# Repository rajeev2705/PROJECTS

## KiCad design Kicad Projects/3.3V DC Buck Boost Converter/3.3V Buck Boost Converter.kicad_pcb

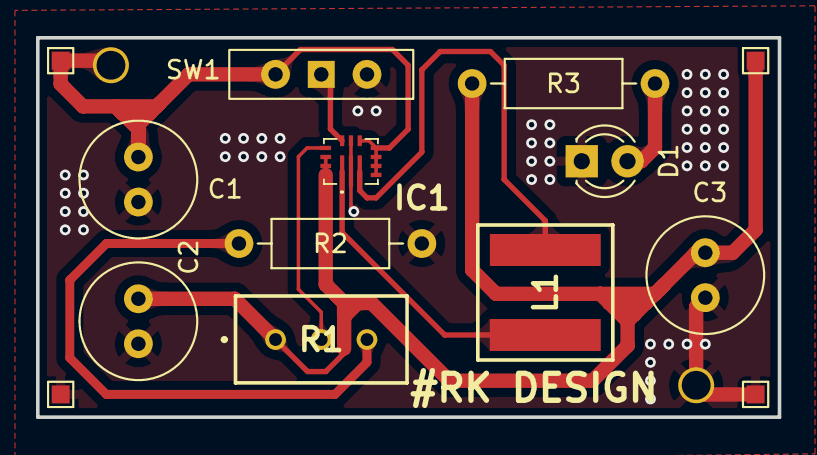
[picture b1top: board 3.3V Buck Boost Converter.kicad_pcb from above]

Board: 2 copper layers, 41.2 x 21.1 mm, 14 parts (0 on the bottom side), 9 nets.

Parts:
C1: 10uF/10V; C_Radial_D6.3mm_H11.0mm_P2.50mm
C2, C3: 22uf/6V3; C_Radial_D6.3mm_H11.0mm_P2.50mm
D1: LED; LED_D3.0mm
IC1: Buck_Boost_TPS63025_SMD; IC_BuckBoost_TPS630250RNCT_VQFN14_2x3mm
J1: VIN+; TestPoint_Pad_1.0x1.0mm
J2: VIN-; TestPoint_Pad_1.0x1.0mm
J3: VOUT+; TestPoint_Pad_1.0x1.0mm
J4: VOUT-; TestPoint_Pad_1.0x1.0mm
L1: L; XFL7015102MEB
R1: PT01-D120K1-B103; TrimPot_10k_SMD
R2: 180k; R_Axial_DIN0207_L6.3mm_D2.5mm_P10.16mm_Horizontal
R3: 1k; R_Axial_DIN0207_L6.3mm_D2.5mm_P10.16mm_Horizontal
SW1: SW_Wuerth_450301014042; SW_Slide-03_Wuerth-WS-SLTV_10x2.5x6.4_P2.54mm

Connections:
3V3: C2.1, C3.1, IC1.12 (VOUT_1), IC1.13 (VOUT_2), IC1.14 (VOUT_3), J3.1, R1.1, R3.1
FB: IC1.11 (FB), R1.2
GND: C1.2, C2.2, C3.2, D1.1 (K), IC1.2 (PGND), IC1.9 (GND), J2.1, J4.1, R2.1, SW1.2 (C)
unnamed: D1.2 (A), R3.2
unnamed: IC1.3 (L1), L1.1
unnamed: IC1.1 (L2), L1.2
unnamed: R1.3, R2.2
PFM/PWM: IC1.10 (PFM/PWM), SW1.1 (B)
VIN+: C1.1, IC1.4 (VIN_1), IC1.5 (VIN_2), IC1.6 (VIN_3), IC1.7 (VINA), IC1.8 (EN), J1.1, SW1.3 (A)

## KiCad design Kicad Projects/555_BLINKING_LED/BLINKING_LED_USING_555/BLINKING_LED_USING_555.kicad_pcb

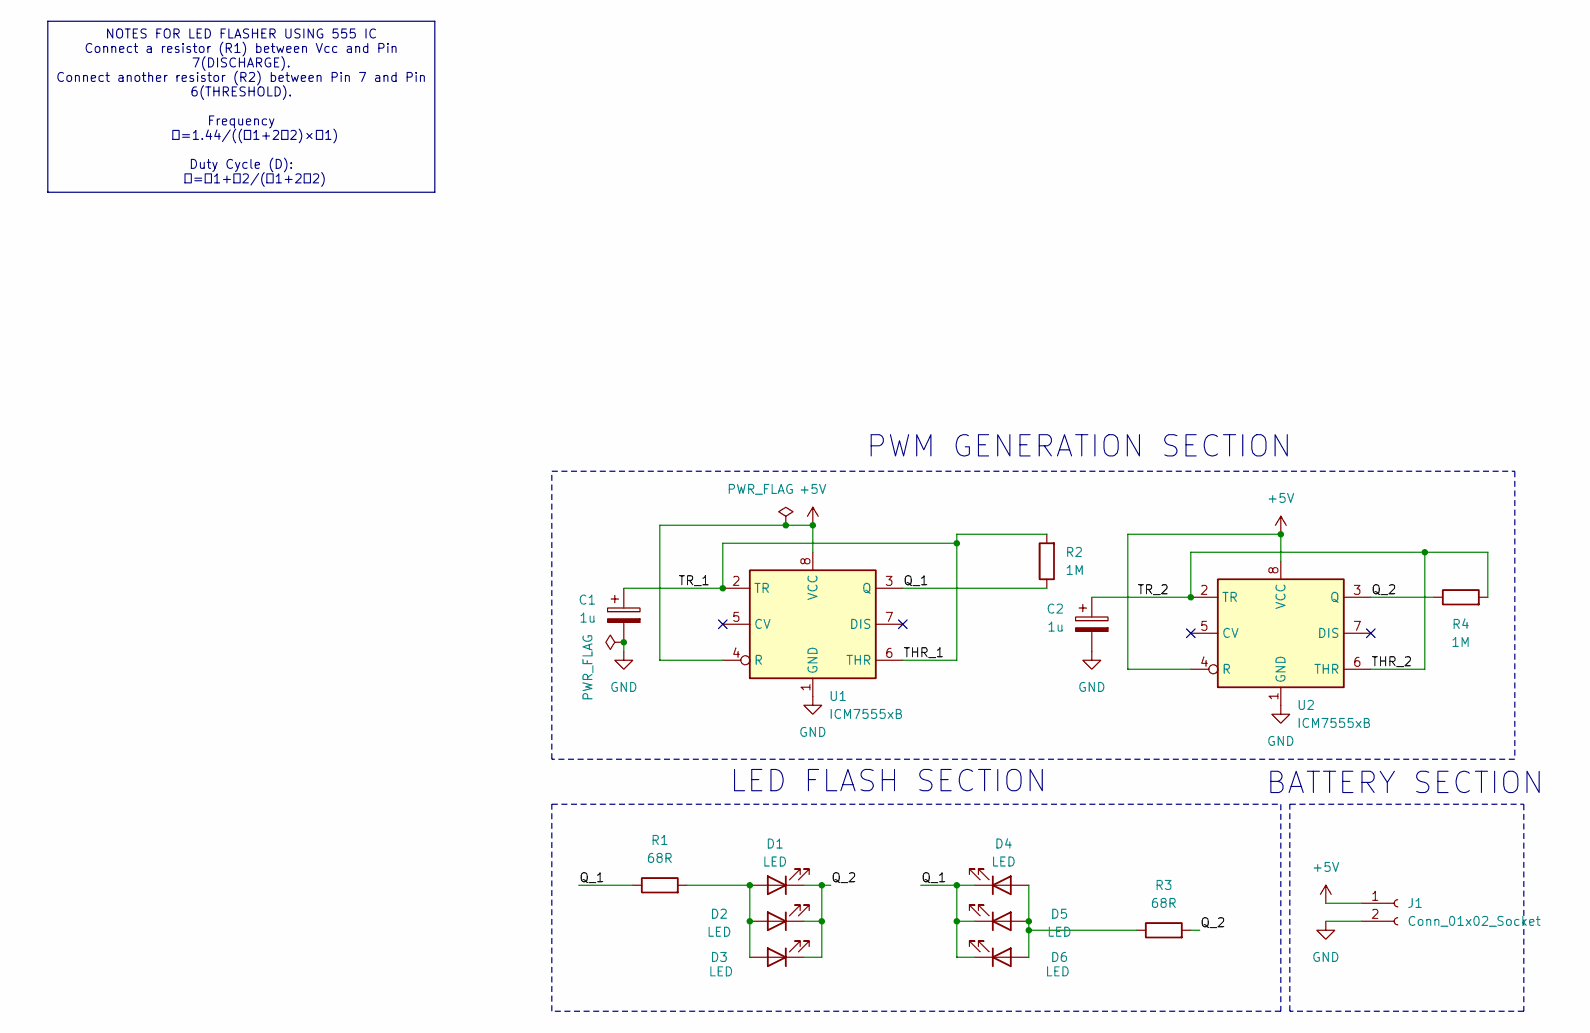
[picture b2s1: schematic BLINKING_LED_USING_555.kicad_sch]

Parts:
C1, C2: 1u; CP_Radial_D4.0mm_P1.50mm
D1, D2, D3, D4, D5, D6: LED; LED_D3.0mm
J1: Conn_01x02_Socket; PinHeader_1x02_P2.54mm_Vertical
R1: 68R; R_Axial_DIN0207_L6.3mm_D2.5mm_P7.62mm_Horizontal
R2, R4: 1M; R_Axial_DIN0207_L6.3mm_D2.5mm_P10.16mm_Horizontal
R3: 68R; R_Axial_DIN0207_L6.3mm_D2.5mm_P10.16mm_Horizontal
U1, U2: ICM7555xB; SOIC-8_3.9x4.9mm_P1.27mm

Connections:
+5V: J1.1, U1.4 (R), U1.8 (VCC), U2.4 (R), U2.8 (VCC)
/Q_1: D4.1 (K), D5.1 (K), D6.1 (K), R1.1, R2.1, U1.3 (Q)
/Q_2: D1.1 (K), D2.1 (K), D3.1 (K), R3.2, R4.1, U2.3 (Q)
/THR_1: C1.1, R2.2, U1.2 (TR), U1.6 (THR)
/THR_2: C2.1, R4.2, U2.2 (TR), U2.6 (THR)
GND: C1.2, C2.2, J1.2, U1.1 (GND), U2.1 (GND)
unnamed: D1.2 (A), D2.2 (A), D3.2 (A), R1.2
unnamed: D4.2 (A), D5.2 (A), D6.2 (A), R3.1

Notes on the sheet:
NOTES FOR LED FLASHER USING 555 IC Connect a resistor (R1) between Vcc and Pin 7(DISCHARGE). Connect another resistor (R2) between Pin 7 and Pin 6(THRESHOLD). Frequency 𝑓=1.44/((𝑅1+2𝑅2)×𝐶1) Duty Cycle (D): 𝐷=𝑅1+𝑅2/(𝑅1+2𝑅2)
LED FLASH SECTION
BATTERY SECTION
PWM GENERATION SECTION

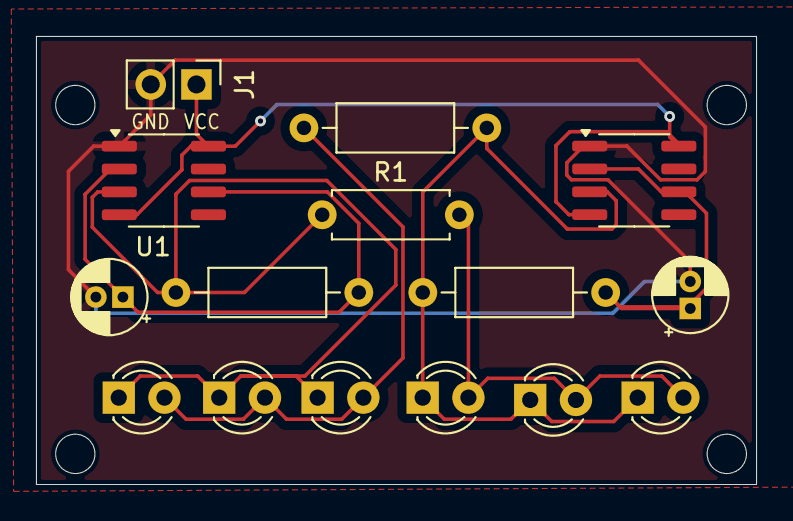
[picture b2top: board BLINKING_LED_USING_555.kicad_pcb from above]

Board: 2 copper layers, 40.0 x 24.9 mm, 15 parts (0 on the bottom side), 8 nets.

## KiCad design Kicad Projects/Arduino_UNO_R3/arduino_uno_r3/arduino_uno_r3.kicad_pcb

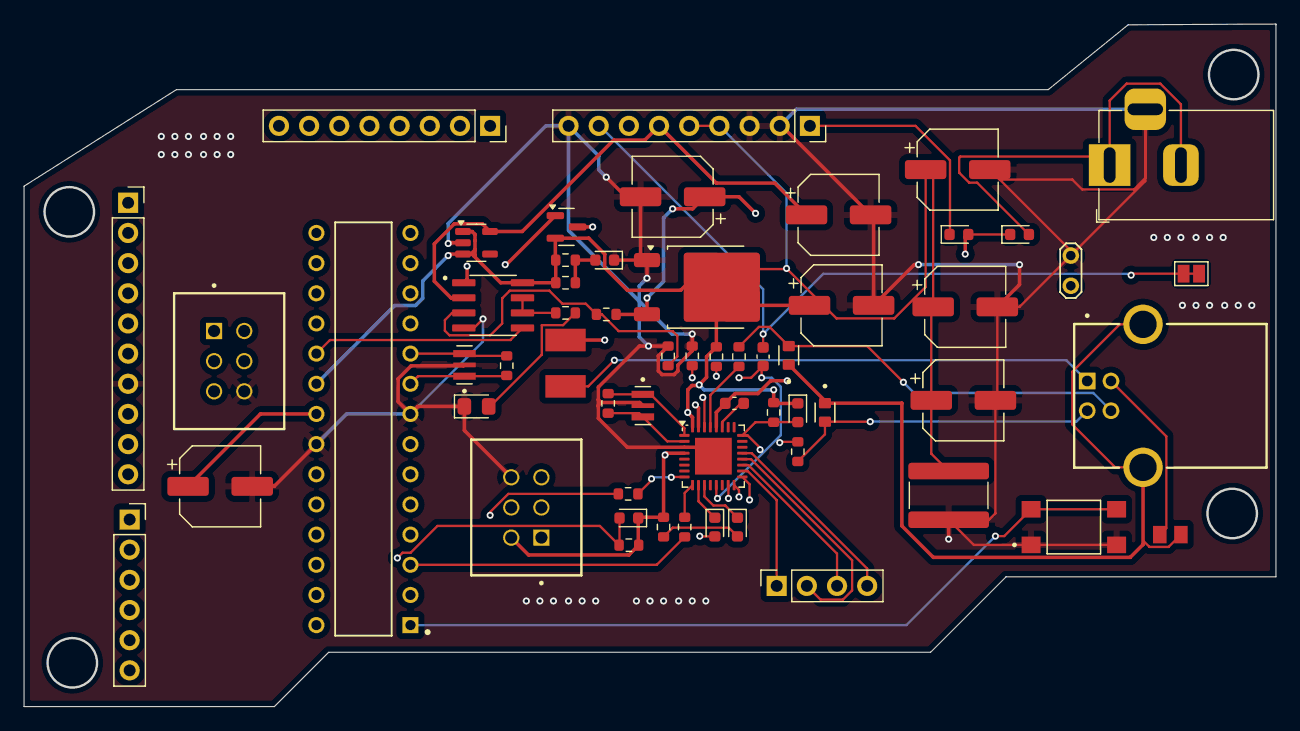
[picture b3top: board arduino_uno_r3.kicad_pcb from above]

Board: 4 copper layers, 105.4 x 57.5 mm, 58 parts (0 on the bottom side), 62 nets.

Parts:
C1, C2: 47u; CP_Elec_6.3x3
C3, C4, C9, C10: 100n; CP_Elec_6.3x3
C5: 1u; CP_Elec_6.3x3
C6: 1u; C_0603_1608Metric
C7: 100n; C_1825_4564Metric
C8: 100n; C_0603_1608Metric
D1, D3, D7, D8: D; D_0603_1608Metric
D2: GREEN ON; LED_0603_1608Metric
D4, D5: LED; LED_0603_1608Metric
D6: LED; LED_0805_2012Metric_Pad1.15x1.40mm_HandSolder
F1: MF-MSMF050-2; FUSM1812X02
FL1: BLM21SP111SH1D; BEADC2012X105N
J1: Barrel_Jack_Switch_Pin3Ring; BarrelJack_Horizontal
J2: Conn_01x09_Socket; PinSocket_1x09_P2.54mm_Vertical
J3: USB-B-S-X-X-TH-TR; SAMTEC_USB-B-S-X-X-TH-TR
J4, J6: ICSP HEADER; SAMTEC_TSS-103-03-L-D
J5: Conn_01x04_Socket; PinSocket_1x04_P2.54mm_Vertical
J7: Conn_01x08_Socket; PinSocket_1x08_P2.54mm_Vertical
J8: Conn_01x10_Socket; PinSocket_1x10_P2.54mm_Vertical
J9: Conn_01x06_Socket; PinSocket_1x06_P2.54mm_Vertical
JP1: SolderJumper_2_Open; SolderJumper-2_P1.3mm_Open_Pad1.0x1.5mm
JP2: SolderJumper_2_Open; TestPoint_2Pads_Pitch2.54mm_Drill0.8mm
Q1: FDN340P; SOT-23
R1A1, R1B1, R8, R9, R11, R12, R15, R16: 1k; R_0603_1608Metric
R3, R4, R5, R14: 10k; R_0603_1608Metric
R6, R7: 22R; R_0603_1608Metric
R10, R13: 1M; R_0603_1608Metric
RV1, RV2: CG0603MLC-05E; VARC1608X56N
S1: TL3305CF160QG; SW_TL3305CF160QG
U1: NCP1117-5.0_TO252; TO-252-2
U3: LP2985-3.3; SOT-23-5
U4: ATmega16U2-M; QFN-32-1EP_5x5mm_P0.5mm_EP3.1x3.1mm
U6: LMV358; SOIC127P599X175-8N
U7: ATMEGA328P-PU; DIP794W46P254L2967H457Q28B
Y1, Y2: CSTCE16M0V53-R0; OSC_CSTCE16M0V53-R0

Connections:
+5V: C2.1, C3.1, C4.1, C7.2, C10.1, D3.1 (K), D7.1 (K), J2.4, J2.5, J4.02, J6.02, Q1.2 (S), R1A1.2, R1B1.2, R5.2, R8.1, R9.1, R14.2, U1.2 (VO), U3.1 (VIN), U3.3 (ON/~OFF), U4.4 (VCC), U4.32 (AVCC), U6.8 (V+), U7.7 (VCC), U7.20 (AVCC)
/MCU/AREF: C9.1, J8.8, U7.21 (AREF)
/MCU/IO0/RXD: J7.1, R15.1, U7.2 (PD0)
/MCU/IO1/TXD: J7.2, R16.1, U7.3 (PD1)
/MCU/IO2: J7.3, U7.4 (PD2)
/MCU/IO3: J7.4, U7.5 (PD3)
/MCU/IO4: J7.5, U7.6 (PD4)
/MCU/IO5: J7.6, U7.11 (PD5)
/MCU/IO6: J7.7, U7.12 (PD6)
/MCU/IO7: J7.8, U7.13 (PD7)
/MCU/IO8: J8.1, U7.14 (PB0)
/MCU/IO9: J8.2, U7.15 (PB1)
/MCU/PB3/MOSI: J6.04, J8.4, U7.17 (PB3)
/MCU/PB4/MISO: J6.01, J8.5, U7.18 (PB4)
/MCU/PB5/SCK: J6.03, J8.6, U6.5 (+), U7.19 (PB5)
/MCU/PC0: J9.1, U7.23 (PC0)
/MCU/PC1: J9.2, U7.24 (PC1)
/MCU/PC2: J9.3, U7.25 (PC2)
/MCU/PC3: J9.4, U7.26 (PC3)
/MCU/PC4/SDA: J8.9, J9.5, U7.27 (PC4)
/MCU/PC5/SCL: J8.10, J9.6, U7.28 (PC5)
/MCU/RESET: D7.2 (A), J6.05, R14.1, S1.3, S1.4, U7.1 (PC6/~RESET)
/MCU/SS: J8.3, U7.16 (PB2)
/POWER SEC/+3.3V: C5.1, J2.6, U3.5 (VOUT), U6.2 (-)
/POWER SEC/GATE_CONTROL: Q1.1 (G), U6.1
/POWER SEC/PWRIN: D1.2 (A), J1.1, J1.2
/POWER SEC/VIN: C1.1, D1.1 (K), D8.2 (A), J2.7, R3.1, U1.3 (VI)
/USB SECTION/AT_TO_CAP: C6.1, U4.27 (UCAP)
/USB SECTION/MCUD+: R7.1, U4.29 (D+)
/USB SECTION/MCUD-: R6.1, U4.30 (D-)
/USB SECTION/MISO2: J4.01, U4.17 (PB3)
/USB SECTION/MOSI2: J4.04, U4.16 (PB2)
/USB SECTION/PB4: J5.1, U4.18 (PB4)
/USB SECTION/PB5: J5.3, U4.19 (PB5)
/USB SECTION/PB6: J5.2, U4.20 (PB6)
/USB SECTION/PB7: J5.4, U4.21 (PB7)
/USB SECTION/PD7: C8.2, R11.2, U4.13 (~HWB/PD7)
/USB SECTION/RESET2: D3.2 (A), J4.05, R5.1, U4.24 (PC1/~RESET)
/USB SECTION/SCK2: J4.03, U4.15 (PB1)
/USB SECTION/USBD+: J3.3 (D+), R7.2, RV2.2
/USB SECTION/USBD-: J3.2 (D-), R6.2, RV1.2
/USB SECTION/USBGND: C6.2, FL1.2, J3.4 (GND), JP2.1 (A), U4.28 (UGND)
/USB SECTION/USBSHIELD: FL1.1, J3.S1 (SHIELD), J3.S2 (SHIELD), RV1.1, RV2.1
GND: C1.2, C2.2, C3.2, C4.2, C5.2, C7.1, C9.2, C10.2, D2.1 (K), D6.1 (K), J1.3, J2.2, J2.3, J2.9, J4.06, J6.06, J8.7, JP2.2 (B), R4.1, R11.1, S1.1, S1.2, U1.1 (GND), U3.2 (GND), U4.3 (GND), U4.33 (GND), U6.4 (V-), U7.8 (GND), U7.22 (GND), Y1.2, Y2.2
unnamed: D2.2 (A), R1A1.1, R1B1.1
unnamed: D4.2 (A), R8.2
unnamed: D5.2 (A), R9.2
unnamed: D6.2 (A), R12.2
unnamed: D8.1 (K), J2.1
unnamed: F1.1, J3.1 (VCC)
unnamed: R10.2, U4.2 (PC0/XTAL2), Y1.3
unnamed: R10.1, U4.1 (XTAL1), Y1.1
unnamed: R3.2, R4.2, U6.3 (+)
unnamed: R12.1, U6.6 (-), U6.7
unnamed: R13.1, U7.9 (PB6), Y2.1
unnamed: R13.2, U7.10 (PB7), Y2.3
RESET: C8.1, J2.8, JP1.1 (A), JP1.2 (B)
RXLED: D5.1 (K), U4.10 (PD4)
RXM8: R15.2, U4.8 (PD2)
TXLED: D4.1 (K), U4.11 (PD5)
TXM8: R16.2, U4.9 (PD3)
USBVCC: F1.2, Q1.3 (D), U4.31 (UVCC)

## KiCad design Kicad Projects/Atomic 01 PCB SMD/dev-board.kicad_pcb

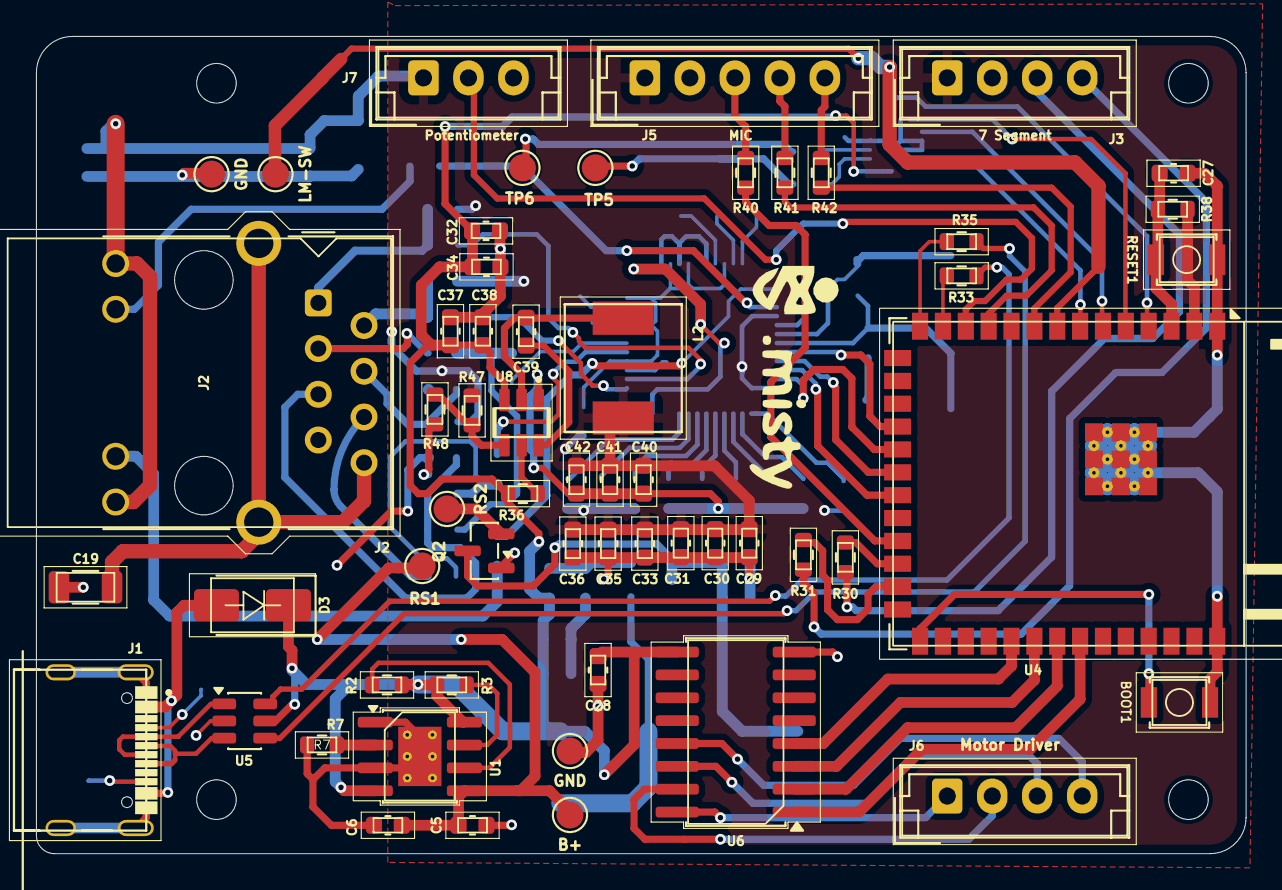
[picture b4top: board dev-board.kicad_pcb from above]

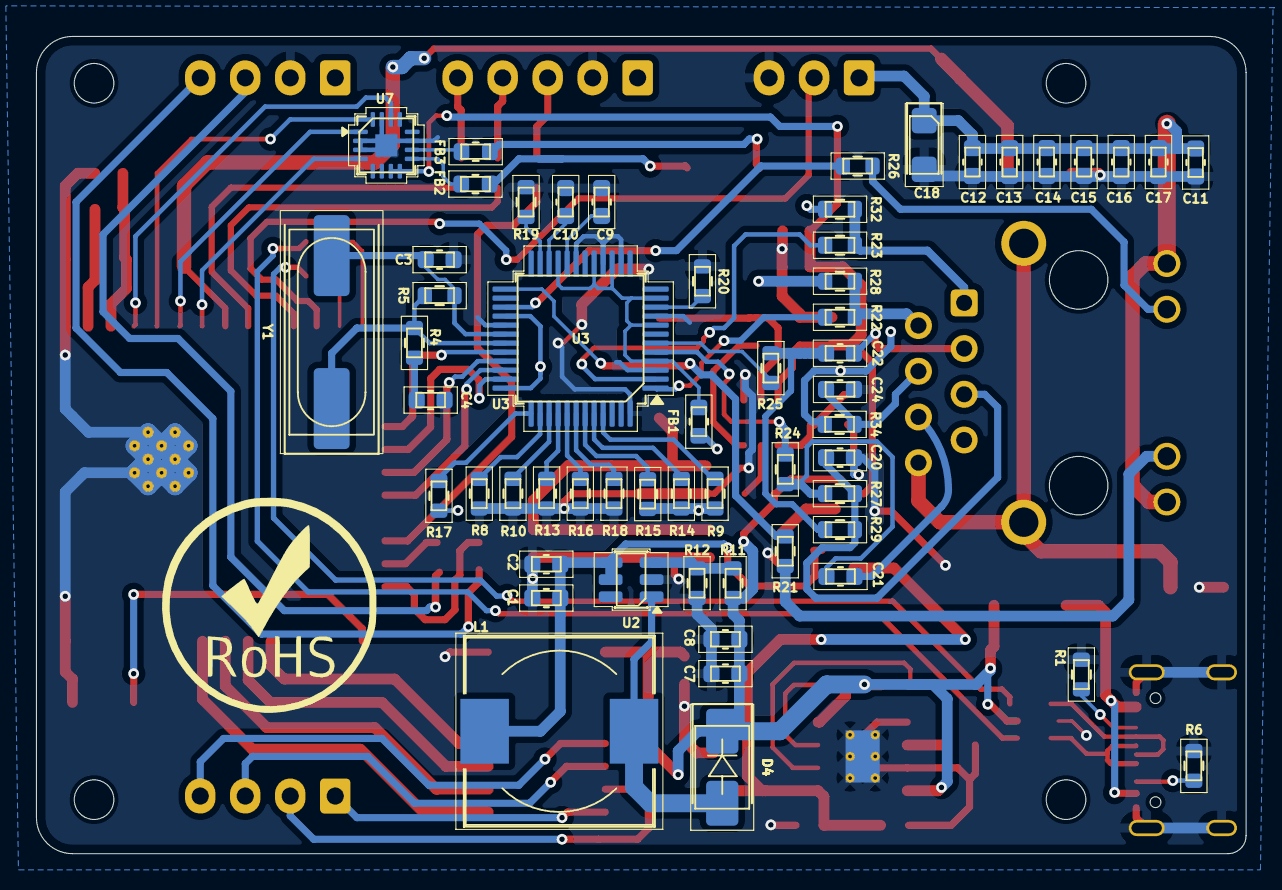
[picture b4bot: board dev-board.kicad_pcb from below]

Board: 2 copper layers, 67.2 x 45.4 mm, 118 parts (57 on the bottom side), 92 nets.

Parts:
B+: BAT+; TestPoint_Pad_D1.5mm
BOOT1: TS-1088-AR02016; SW_SPST_B3U-1000P
C1, C5, C8, C28, C37, C38: 10uf; C_0603_1608Metric
C2, C6, C7, C11, C12, C13, C14, C15, C29, C30, C32, C35, C39: 0.1uf; C_0603_1608Metric
C3, C4: 18pf; C_0603_1608Metric
C9: 4.7uf; C_0603_1608Metric
C10, C20: 10nf; C_0603_1608Metric
C16, C17, C27, C31, C33, C34, C36: 1uf; C_0603_1608Metric
C18: 10uf 16V; CP_EIA-3216-18_Kemet-A
C19: 1nf 2KV; C_1206_3216Metric
C21, C22: 6.8nf; C_0603_1608Metric
C24: 22nf; C_0603_1608Metric
C40, C41, C42: 22uf; C_0603_1608Metric
D3, D4: SS14; D_SMA
FB1: FerriteBead_Small; L_0603_1608Metric
FB2, FB3: Ferrite Bead 0603 600Ω @100MHz ≥1A; L_0603_1608Metric
GND: GND; TestPoint_Pad_D1.5mm
GND#2: BAT-; TestPoint_Pad_D1.5mm
H1, H2, H3, H4: MountingHole; MountingHole_2.2mm_M2
J1: TYPE-C-31-M-12; HRO_TYPE-C-31-M-12
J2: RJ45_Hanrun_HR911105A_Horizontal
J3: 7 Segment; JST_EH_B4B-EH-A_1x04_P2.50mm_Vertical
J5: MIC; JST_EH_B5B-EH-A_1x05_P2.50mm_Vertical
J6: B4B-PH-K-S; JST_EH_B4B-EH-A_1x04_P2.50mm_Vertical
J7: Potentiometer; JST_EH_B3B-EH-A_1x03_P2.50mm_Vertical
L1: 22uH; L_10.4x10.4_H4.8
L2: 2.2uH 15mOhm; IND_SPM6530T-2R2M
LM-SW: LIMIT_SWITCH; TestPoint_Pad_D1.5mm
Q2: AO3401A; SOT-23
R1, R6, R38: 5.1K; R_0603_1608Metric
R2, R3, R8, R9, R10, R13, R14, R15, R16, R17, R18, R19, R36, R48: 10k; R_0603_1608Metric
R4: 0R; R_0603_1608Metric
R5: 1M; R_0603_1608Metric
R7: 3k; R_0603_1608Metric
R11: 15k; R_0603_1608Metric
R12: 2k; R_0603_1608Metric
R20: 12.4k; R_0603_1608Metric
R21, R26: 330; R_0603_1608Metric
R22, R23, R24, R25: 33; R_0603_1608Metric
R27, R29: 49.9; R_0603_1608Metric
R28, R32: 49.1; R_0603_1608Metric
R30, R31: 100R; R_0603_1608Metric
R33, R35, R40, R41, R42: 22R; R_0603_1608Metric
R34: 10; R_0603_1608Metric
R47: 33.2k; R_0603_1608Metric
RESET1: TS-1088-AR02016; SW_SPST_B3U-1000P
RS1, RS2: TestPoint; TestPoint_Pad_D1.5mm
TP5: SpeakerP; TestPoint_Pad_D1.5mm
TP6: SpeakerN; TestPoint_Pad_D1.5mm
U1: TP4056-42-ESOP8; SOIC-8-1EP_3.9x4.9mm_P1.27mm_EP2.41x3.3mm_ThermalVias
U2: MT3608; SOT-23-6
U3: W5500; LQFP-48_7x7mm_P0.5mm
U4: ESP32-S3-WROOM-2
U5: USBLC6-2SC6; SOT-23-6
U6: ULN2003; SOIC-16W_5.3x10.2mm_P1.27mm
U7: MAX98357A; TQFN-16-1EP_3x3mm_P0.5mm_EP1.23x1.23mm
U8: TPS563208DDCR; SOT95P280X110-6N
Y1: 25MHz; Crystal_SMD_HC49-SD

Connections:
+3V3: C11.1, C12.1, C13.1, C14.1, C15.1, C16.1, C17.1, C18.1, C29.1, C30.1, C31.1, C33.1, C35.1, C36.1, C40.1, C41.1, C42.1, FB1.1, J2.9, J2.12, J3.1, J5.1, J7.1, L2.2, R9.1, R14.1, R15.1, R17.1, R28.2, R32.2, R34.2, R38.1, R47.1, U3.28 (VDD), U3.36 (~INT), U4.2 (3V3)
+5V: C7.1, C8.1, C28.1, C32.1, C34.1, C37.1, C38.1, D3.1 (K), D4.1 (K), R2.1, R3.1, R11.2, R36.2, U1.4 (V_{CC}), U1.8 (CE), U5.5 (VBUS), U6.9 (COM), U7.7 (VDD), U7.8 (VDD), U8.3 (VIN)
ACTLED: R26.2, U3.27 (ACTLED)
B+: B+.1, C5.1, C6.1, RS1.1, U1.5 (BAT)
B-Pass: Q2.2 (S), RS2.1
B-Reached: C1.1, C2.1, L1.1, Q2.3 (D), U2.4 (EN), U2.5 (IN)
CLK: J3.3, R30.2
CS: U3.32 (~SCS), U4.18 (IO10)
D+: R35.2, U5.4 (I/O2)
D-: R33.2, U5.6 (I/O1)
DIO: J3.4, R31.2
EN: C27.1, R38.2, RESET1.2, U4.3 (EN)
GND: BOOT1.1, C1.2, C2.2, C3.1, C4.1, C5.2, C6.2, C7.2, C8.2, C9.2, C10.1, C11.2, C12.2, C13.2, C14.2, C15.2, C16.2, C17.2, C18.2, C19.2, C20.1, C24.1, C27.2, C28.2, C29.2, C30.2, C31.2, C32.2, C33.2, C34.2, C35.2, C36.2, C37.2, C38.2, C40.2, C41.2, C42.2, GND.1, GND#2.1, J1.A1_B12 (GND), J1.B1_A12 (GND), J1.S1 (SHIELD), J1.S2 (SHIELD), J1.S3 (SHIELD), J1.S4 (SHIELD), J3.2, J5.2, J7.3, Q2.1 (G), R1.2, R6.2, R7.2, R8.1, R10.1, R12.1, R13.1, R16.1, R18.1, R19.1, R20.2, R48.2, RESET1.1, U1.1 (TEMP), U1.3 (GND), U1.9 (EPAD), U2.2 (GND), U3.3 (AGND), U3.9 (AGND), U3.14 (AGND), U3.16 (AGND), U3.19 (AGND), U3.29 (GND), U3.48 (AGND), U4.1 (GND), U4.40 (GND), U4.41 (GND), U5.2 (GND), U6.8 (GND), U7.2 (GAIN_SLOT), U7.3 (GND), U7.11 (GND), U7.15 (GND), U7.17 (PAD), U8.1 (GND)
GPIO0: BOOT1.2, U4.27 (IO0)
GPIO11: U3.35 (MOSI), U4.19 (IO11)
GPIO12: U3.33 (SCLK), U4.20 (IO12)
GPIO13: U3.34 (MISO), U4.21 (IO13)
IO4: U4.4 (IO4), U7.14 (LRCLK)
IO5: U4.5 (IO5), U7.16 (BCLK)
IO6: U4.6 (IO6), U7.1 (DIN)
IO7: U4.7 (IO7), U7.4 (~SD_MODE)
IO8: J7.2, U4.12 (IO8)
IO38: U4.31 (IO38), U6.4 (I4)
IO39: U4.32 (MTCK/IO39), U6.3 (I3)
IO40: U4.33 (MTDO/IO40), U6.2 (I2)
IO41: U4.34 (MTDI/IO41), U6.1 (I1)
LIMIT_SWITCH: LM-SW.1, U4.8 (IO15)
LINKLED: R21.2, U3.25 (LINKLED)
unnamed: C4.2, R4.2
unnamed: C19.1, J2.8, J2.SH
unnamed: C21.1, R24.2, R27.1
unnamed: C22.1, R25.2, R29.1
unnamed: D3.2 (A), J1.A4_B9 (VBUS), J1.B4_A9 (VBUS)
unnamed: D4.2 (A), L1.2, U2.1 (SW)
unnamed: FB1.2, U3.4 (AVDD), U3.8 (AVDD), U3.11 (AVDD), U3.15 (AVDD), U3.17 (AVDD), U3.21 (AVDD)
unnamed: FB2.2, TP5.1
unnamed: FB3.2, TP6.1
unnamed: J1.A5 (CC1), R1.1
unnamed: J1.B5 (CC2), R6.1
unnamed: J2.10, R26.1
unnamed: J2.11, R21.1
unnamed: J5.3, R40.2
unnamed: J5.4, R41.2
unnamed: J5.5, R42.2
unnamed: R8.2, U3.38 (RSVD)
unnamed: R10.2, U3.39 (RSVD)
unnamed: R13.2, U3.40 (RSVD)
unnamed: R16.2, U3.41 (RSVD)
unnamed: R18.2, U3.42 (RSVD)
unnamed: R19.2, U3.23 (RSVD)
unnamed: R7.1, U1.2 (PROG)
unnamed: R3.2, U1.7 (~CHRG)
unnamed: R2.2, U1.6 (~STDBY)
unnamed: R11.1, R12.2, U2.3 (FB)
unnamed: C10.2, U3.22 (1V2O)
unnamed: R20.1, U3.10 (EXRES1)
unnamed: R9.2, U3.45 (PMODE0)
unnamed: R14.2, U3.44 (PMODE1)
unnamed: R15.2, U3.43 (PMODE2)
unnamed: C9.1, U3.20 (TOCAP)
unnamed: R17.2, U3.37 (~RST)
unnamed: R30.1, U4.24 (IO47)
unnamed: R31.1, U4.25 (IO48)
unnamed: R35.1, U4.14 (USB_D+/IO20)
unnamed: R33.1, U4.13 (USB_D-/IO19)
unnamed: FB3.1, U7.10 (OUTN)
unnamed: FB2.1, U7.9 (OUTP)
unnamed: R36.1, U8.5 (EN)
unnamed: C39.1, L2.1, U8.2 (SW)
unnamed: C39.2, U8.6 (VBST)
unnamed: R47.2, R48.1, U8.4 (VFB)
O1: J6.1, U6.16 (O1)
O2: J6.2, U6.15 (O2)
O3: J6.3, U6.14 (O3)
O4: J6.4, U6.13 (O4)
RCT: C20.2, J2.5 (RCT), R27.2, R29.2
RD+: C22.2, J2.3 (RD+)
RD-: C21.2, J2.6 (RD-)
RXN: R24.1, U3.5 (RXN)
RXP: R25.1, U3.6 (RXP)
SCK-MIC: R40.1, U4.23 (IO21)
SD-MIC: R42.1, U4.9 (IO16)
TCT: C24.2, J2.4 (TCT), R34.1
TD+: J2.1 (TD+), R23.2, R32.1
TD-: J2.2 (TD-), R22.2, R28.1
TXN: R22.1, U3.1 (TXN)
TXP: R23.1, U3.2 (TXP)
USBD+: J1.A6 (DP1), J1.B6 (DP2), U5.3 (I/O2)
USBD-: J1.A7 (DN1), J1.B7 (DN2), U5.1 (I/O1)
WS-MIC: R41.1, U4.11 (IO18)
XI: C3.2, R5.2, U3.30 (XI/CLKIN), Y1.2
XO: R4.1, R5.1, U3.31 (XO), Y1.1

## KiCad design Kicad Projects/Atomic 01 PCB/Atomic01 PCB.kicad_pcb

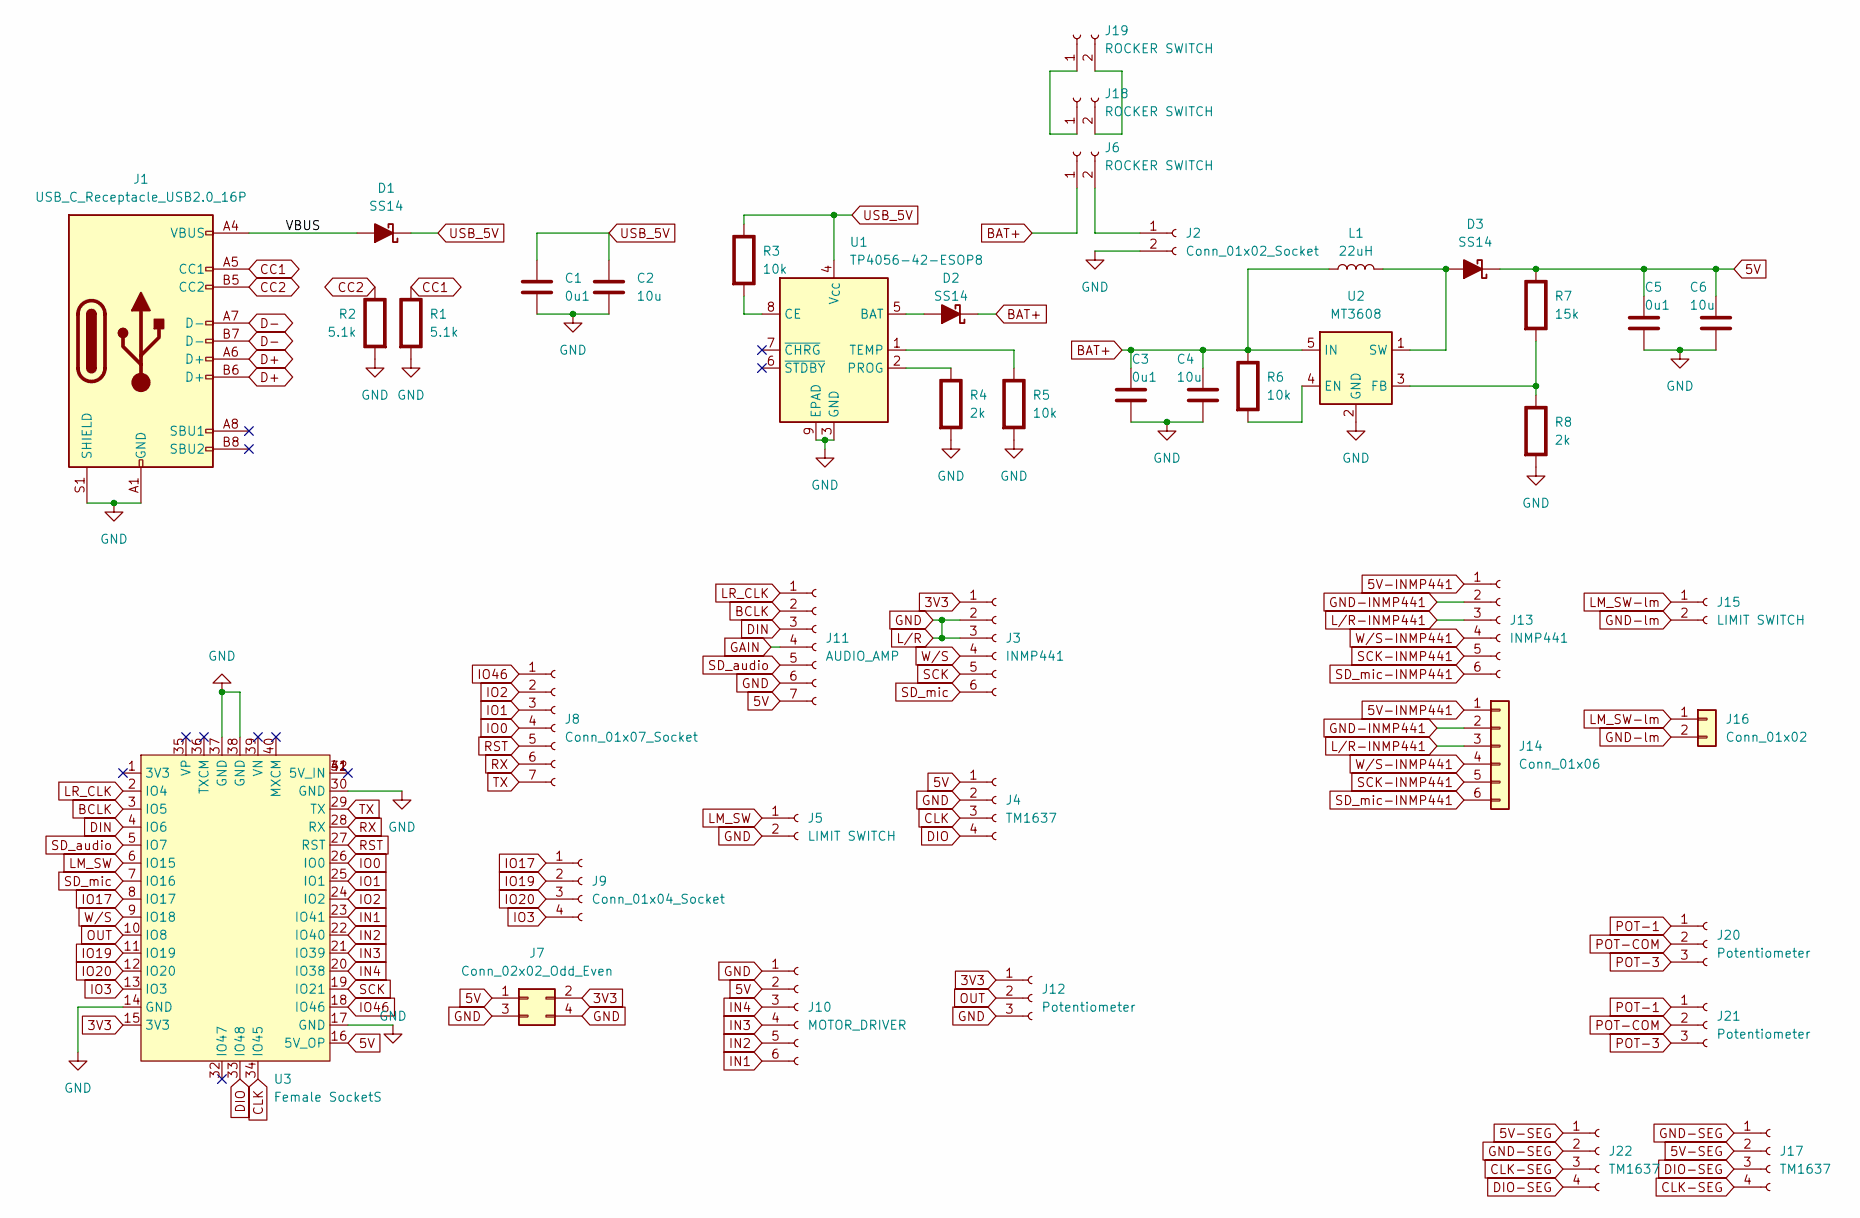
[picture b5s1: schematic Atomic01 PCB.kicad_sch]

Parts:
C1, C3: 0u1; C_0805_2012Metric_Pad1.18x1.45mm_HandSolder
C2, C4: 10u; C_0805_2012Metric_Pad1.18x1.45mm_HandSolder
C5: 0u1; C_0805_2012Metric
C6: 10u; C_0805_2012Metric
D1, D2, D3: SS14; D_SMA
J1: USB_C_Receptacle_USB2.0_16P; USB_C_Receptacle_GCT_USB4105-xx-A_16P_TopMnt_Horizontal
J2: Conn_01x02_Socket; PinSocket_1x02_P2.54mm_Vertical
J3, J13: INMP441; JST_XH_B6B-XH-A_1x06_P2.50mm_Vertical
J4, J22: TM1637; JST_XH_B4B-XH-A_1x04_P2.50mm_Vertical
J5, J15: LIMIT SWITCH; JST_XH_B2B-XH-A_1x02_P2.50mm_Vertical
J6, J19: ROCKER SWITCH; JST_XH_B2B-XH-A_1x02_P2.50mm_Vertical
J7: Conn_02x02_Odd_Even; Harwin_LTek-Male_2x02_P2.00mm_Vertical
J8: Conn_01x07_Socket; PinHeader_1x07_P2.54mm_Vertical
J9: Conn_01x04_Socket; PinHeader_1x04_P2.54mm_Vertical
J10: MOTOR_DRIVER; PinHeader_1x06_P2.54mm_Vertical
J11: AUDIO_AMP; PinHeader_1x07_P2.54mm_Vertical
J12, J21: Potentiometer; JST_XH_B3B-XH-A_1x03_P2.50mm_Vertical
J14: Conn_01x06; inmp441; Part Number 1-0601FBV0T
J16: Conn_01x02; LIMIT SWITCH; Part Number 1-0201FBV0T
J17: TM1637; PinHeader_1x04_P2.54mm_Vertical
J18: ROCKER SWITCH
J20: Potentiometer; Potentiometer_Piher_T-16H_Single_Horizontal
L1: 22uH; L_10.4x10.4_H4.8
R1, R2: 5.1k; R_0805_2012Metric_Pad1.20x1.40mm_HandSolder; Rating W
R3, R5: 10k; R_0805_2012Metric_Pad1.20x1.40mm_HandSolder; Rating W
R4, R8: 2k; R_0805_2012Metric_Pad1.20x1.40mm_HandSolder; Rating W
R6: 10k; C_0805_2012Metric_Pad1.18x1.45mm_HandSolder; Rating W
R7: 15k; R_0805_2012Metric_Pad1.20x1.40mm_HandSolder; Rating W
U1: TP4056-42-ESOP8; SOIC-8-1EP_3.9x4.9mm_P1.27mm_EP2.41x3.3mm_ThermalVias
U2: MT3608; SOT-23-6
U3: Female SocketS; ESP32 S3 LILYGO E TH LITE

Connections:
3V3: J3.1, J7.2, J12.1, U3.15 (3V3)
5V: C5.1, C6.1, D3.1 (K), J4.1, J7.1, J10.2, J11.7, R7.1 (+), U3.16 (5V_OP)
5V-INMP441: J13.1, J14.1
5V-SEG: J17.2, J22.1
/VBUS: D1.2 (A), J1.A4 (VBUS), J1.A9 (VBUS), J1.B4 (VBUS), J1.B9 (VBUS)
BAT+: C3.1, C4.1, D2.1 (K), J6.1, L1.1, R6.1 (+), U2.5 (IN)
BCLK: J11.2, U3.3 (IO5)
CC1: J1.A5 (CC1), R1.1 (+)
CC2: J1.B5 (CC2), R2.1 (+)
CLK: J4.3, U3.34 (IO45)
CLK-SEG: J17.4, J22.3
D+: J1.A6 (D+), J1.B6 (D+)
D-: J1.A7 (D-), J1.B7 (D-)
DIN: J11.3, U3.4 (IO6)
DIO: J4.4, U3.33 (IO48)
DIO-SEG: J17.3, J22.4
GAIN: J11.4
GND: C1.2, C2.2, C3.2, C4.2, C5.2, C6.2, J1.A1 (GND), J1.A12 (GND), J1.B1 (GND), J1.B12 (GND), J1.S1 (SHIELD), J2.2, J3.2, J3.3, J4.2, J5.2, J7.3, J7.4, J10.1, J11.6, J12.3, R1.2 (-), R2.2 (-), R4.2 (-), R5.2 (-), R8.2 (-), U1.3 (GND), U1.9 (EPAD), U2.2 (GND), U3.14 (GND), U3.17 (GND), U3.30 (GND), U3.37 (GND), U3.38 (GND)
GND-INMP441: J13.2, J14.2
GND-SEG: J17.1, J22.2
GND-lm: J15.2, J16.2
IN1: J10.6, U3.23 (IO41)
IN2: J10.5, U3.22 (IO40)
IN3: J10.4, U3.21 (IO39)
IN4: J10.3, U3.20 (IO38)
IO0: J8.4, U3.26 (IO0)
IO1: J8.3, U3.25 (IO1)
IO2: J8.2, U3.24 (IO2)
IO3: J9.4, U3.13 (IO3)
IO17: J9.1, U3.8 (IO17)
IO19: J9.2, U3.11 (IO19)
IO20: J9.3, U3.12 (IO20)
IO46: J8.1, U3.18 (IO46)
LM_SW: J5.1, U3.6 (IO15)
LM_SW-lm: J15.1, J16.1
LR_CLK: J11.1, U3.2 (IO4)
L/R-INMP441: J13.3, J14.3
unnamed: D2.2 (A), U1.5 (BAT)
unnamed: D3.2 (A), L1.2, U2.1 (SW)
unnamed: J2.1, J6.2
unnamed: J18.1, J19.1
unnamed: J18.2, J19.2
unnamed: R3.2 (-), U1.8 (CE)
unnamed: R4.1 (+), U1.2 (PROG)
unnamed: R5.1 (+), U1.1 (TEMP)
unnamed: R6.2 (-), U2.4 (EN)
unnamed: R7.2 (-), R8.1 (+), U2.3 (FB)
OUT: J12.2, U3.10 (IO8)
POT-1: J20.1, J21.1
POT-3: J20.3, J21.3
POT-COM: J20.2, J21.2
RST: J8.5, U3.27 (RST)
RX: J8.6, U3.28 (RX)
SCK: J3.5, U3.19 (IO21)
SCK-INMP441: J13.5, J14.5
SD_audio: J11.5, U3.5 (IO7)
SD_mic: J3.6, U3.7 (IO16)
SD_mic-INMP441: J13.6, J14.6
TX: J8.7, U3.29 (TX)
USB_5V: C1.1, C2.1, D1.1 (K), R3.1 (+), U1.4 (V_{CC})
W/S: J3.4, U3.9 (IO18)
W/S-INMP441: J13.4, J14.4

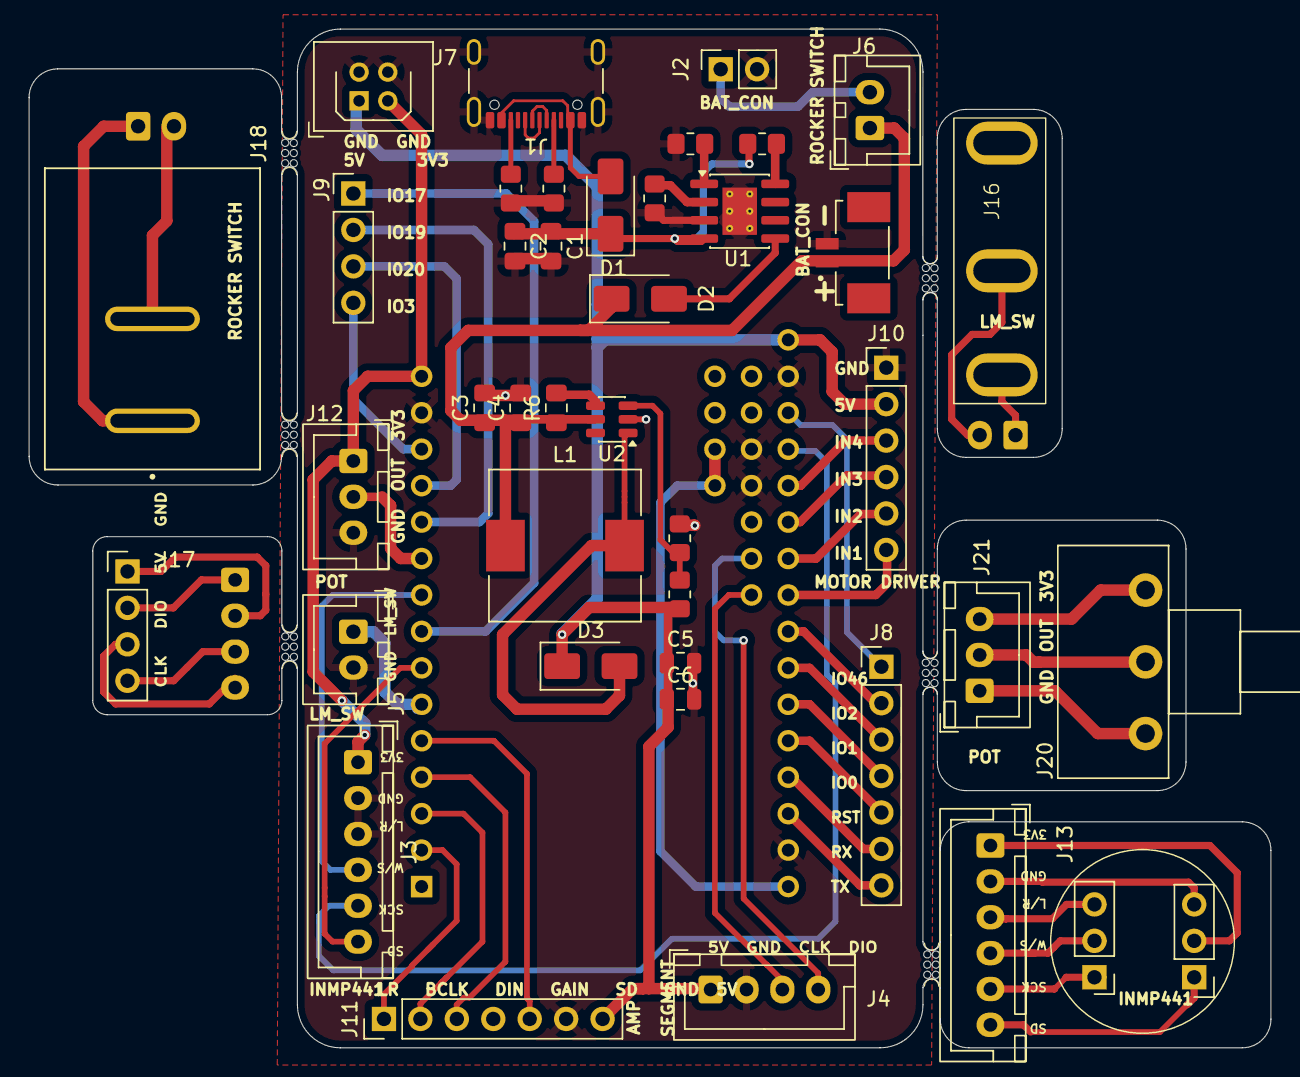
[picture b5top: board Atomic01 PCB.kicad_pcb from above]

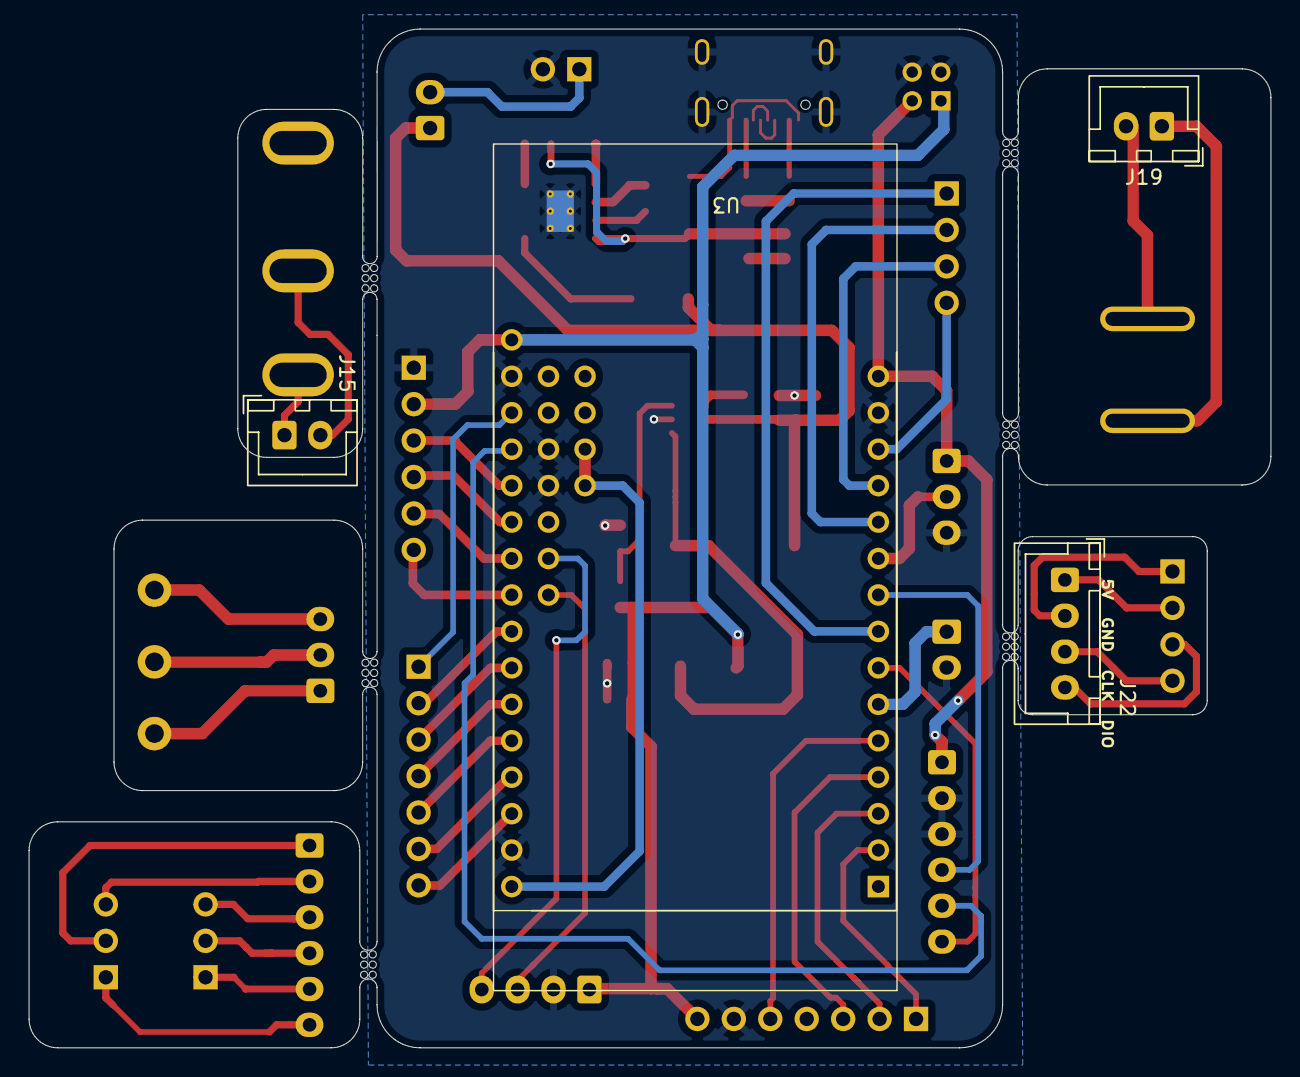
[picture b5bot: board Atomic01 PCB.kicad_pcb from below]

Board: 2 copper layers, 86.5 x 71.0 mm, 49 parts (4 on the bottom side), 61 nets.

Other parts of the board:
mouse-bite-1mm-3mm, mouse-bite-1mm-3mm#2, mouse-bite-1mm-3mm#3, mouse-bite-1mm-3mm#4, mouse-bite-1mm-3mm#5, mouse-bite-1mm-3mm#6: VAL**; mouse-bite-1mm-3mm
